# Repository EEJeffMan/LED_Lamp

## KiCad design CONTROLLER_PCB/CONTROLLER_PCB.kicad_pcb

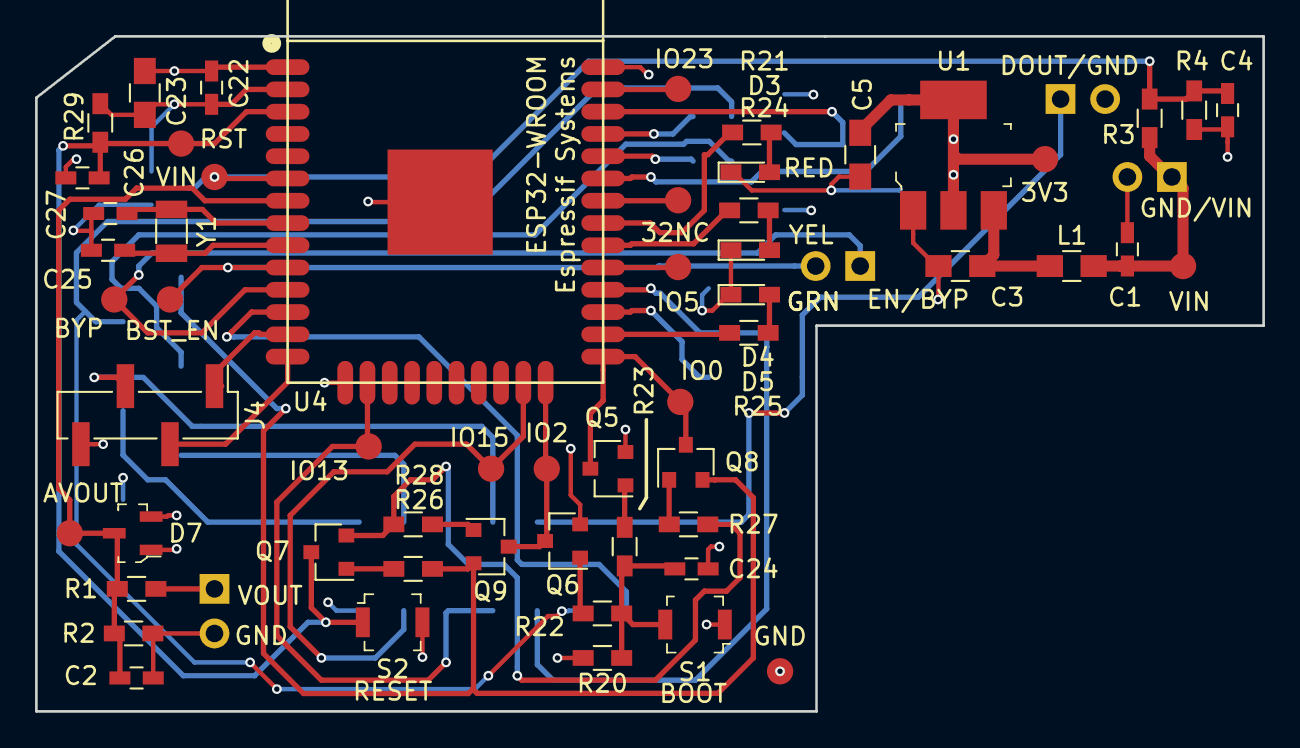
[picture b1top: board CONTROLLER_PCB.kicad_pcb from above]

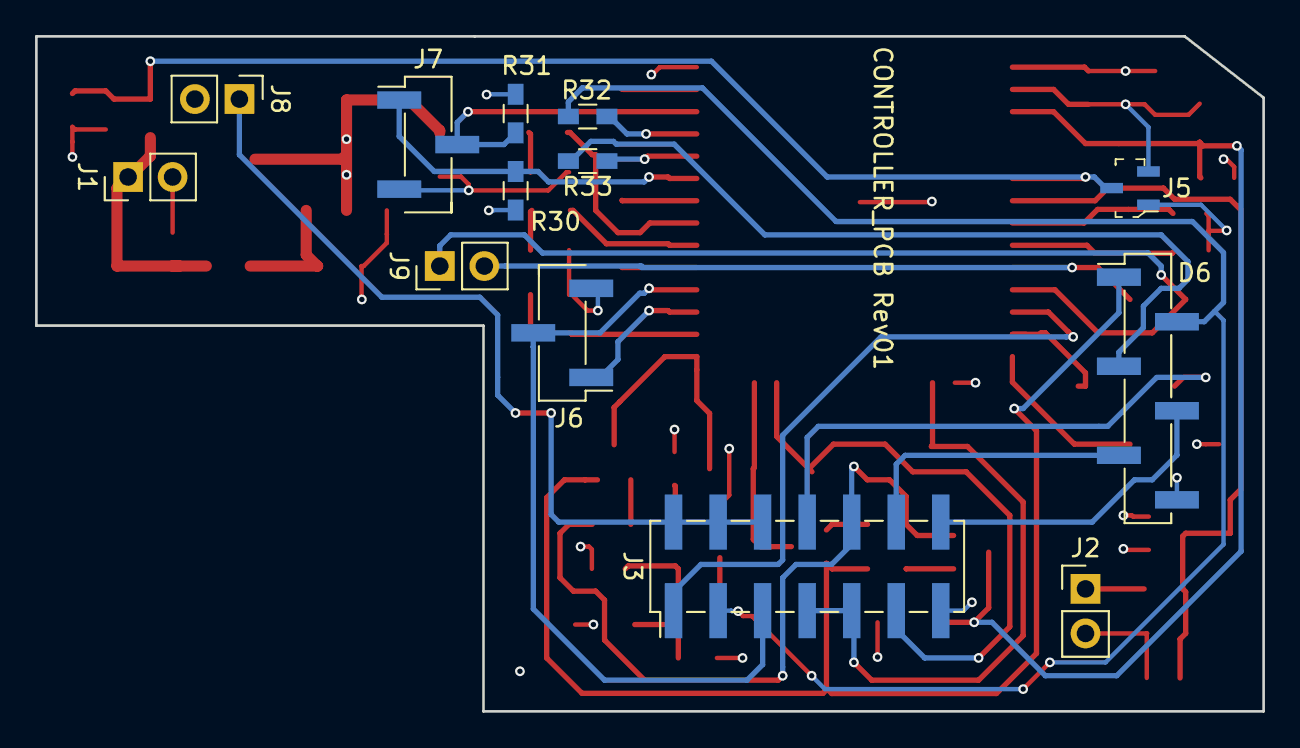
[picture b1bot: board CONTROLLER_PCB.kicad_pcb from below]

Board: 4 copper layers, 70.0 x 38.5 mm, 69 parts (13 on the bottom side), 48 nets.

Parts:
3V3, 32NC: TEST; Measurement_Point_Round-SMD-Pad_Small
AVOUT: TEST; Measurement_Point_Round-SMD-Pad_Small
BST_EN: TEST; Measurement_Point_Round-SMD-Pad_Small
BYP: TEST; Measurement_Point_Round-SMD-Pad_Small
C1, C2, C4, C22, C24, C27: 0.1uF; C_0603_HandSoldering
C3, C5, C23: 10uF; C_0805_HandSoldering
C25, C26: C_Small; C_0603_HandSoldering
D3: Red; LED_0603_HandSoldering
D4: Yellow; LED_0603_HandSoldering
D5: Green; LED_0603_HandSoldering
D6, D7: BAT54S-7-F; SOT-23-3
GND: TEST; Measurement_Point_Round-SMD-Pad_Small
IO0, IO2, IO5, IO13, IO15, IO23: TEST; Measurement_Point_Round-SMD-Pad_Small
J1, J2, J8, J9: Conn_01x02; Pin_Header_Straight_1x02_Pitch2.54mm
J3: Conn_02x07_Odd_Even; Pin_Header_Straight_2x07_Pitch2.54mm_SMD
J4: Conn_01x04; Pin_Header_Straight_1x04_Pitch2.54mm_SMD_Pin1Left
J5: Conn_01x06; Pin_Header_Straight_1x06_Pitch2.54mm_SMD_Pin1Left
J6, J7: Conn_01x03; Pin_Header_Straight_1x03_Pitch2.54mm_SMD_Pin1Left
L1: Ferrite_Bead; C_0805_HandSoldering
Q5, Q6: Q_NMOS_GSD; SOT-23
Q7, Q8, Q9: Q_NPN_BEC; SOT-23
R1, R3, R21, R22, R23, R24, R25, R26, R27, R28, R29: 10k; R_0603_HandSoldering
R2: 1k; R_0603_HandSoldering
R4: 2.49k; R_0603_HandSoldering
R20: 100k; R_0603_HandSoldering
R30, R31: 2.2k; R_0603_HandSoldering
R32, R33: 0 OHM; R_0603_HandSoldering
RST: TEST; Measurement_Point_Round-SMD-Pad_Small
S1, S2: B3U-1000P; Switch_Tactile_SMD_B3U-1000P
U1: AZ1117CH-3_3TRG1; SOT-223
U4: ESP32-WROOM
VIN: TEST; Measurement_Point_Round-SMD-Pad_Small
VIN#2: TEST; Measurement_Point_Round-SMD-Pad_Small
Y1: 32.768 kHz; Crystal_SMD_3215-2pin_3.2x1.5mm

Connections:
3V3_UART: J3.14, J5.4
32KHZ_IN: C26.1, U4.8, Y1.2
32KHZ_OUT: C25.1, U4.9, Y1.1
+3V3: 3V3.1, C5.1, C22.1, C23.1, D6.2, D7.2, J3.13, R29.1, R30.1, R31.1, S1.1, U1.2, U1.4, U4.2
ADC_VIN: C4.1, D6.3, R3.2, R4.1, RST.1, U4.6
ADC_VOUT: AVOUT.1, C2.1, D7.3, R1.2, R2.1, U4.7
BOOST_BYPASS: BYP.1, J9.1, U4.11
BOOST_EN: BST_EN.1, J9.2, U4.10
DOUT: J3.2, J3.4, J3.6, J8.1
DO_0: J3.1, U4.12
GND: C1.2, C2.2, C3.2, C4.2, C5.2, C22.2, C23.2, C24.2, C25.2, C26.2, C27.2, D3.1, D4.1, D5.1, D6.1, D7.1, GND.1, J1.2, J2.2, J4.4, J5.6, J6.3, J7.3, J8.2, Q5.2, Q6.2, R2.2, R4.2, R20.2, S2.2, U1.1, U4.1, U4.15, U4.38, U4.39
I2C_SCL: J7.2, R31.2, U4.36
I2C_SDA: J7.1, R30.2, U4.33
IO0: IO0.1, Q5.3, Q8.3, U4.25
IO2: IO2.1, Q6.3, Q9.3, U4.24
IO13: IO13.1, J3.7, J3.9, U4.16
IO15: IO15.1, J3.11, U4.23
LED_GREEN: R25.1, U4.26
LED_RED: R21.1, U4.31
LED_YELLOW: R24.1, U4.30
unnamed: C3.1, L1.1, U1.3
unnamed: C24.1, R20.1, R22.1, R23.1, S1.2
unnamed: D3.2, R21.2
unnamed: D4.2, R24.2
unnamed: D5.2, R25.2
unnamed: J2.1, R1.1
unnamed: Q5.1, R23.2
unnamed: Q6.1, R22.2
unnamed: Q7.1, R26.2
unnamed: Q8.1, R27.2
unnamed: Q9.1, R28.2
unnamed: R32.1, U4.35
unnamed: R33.1, U4.34
unnamed: IO23.1, U4.37
unnamed: 32NC.1, U4.32
unnamed: IO5.1, U4.29
RXDI: J5.3, R33.2
SPI_MISO: J4.2, U4.14
SPI_MOSI: J3.8, J4.3
SPI_SCK: J4.1, U4.13
TXDO: J3.3, J5.2, R32.2
U2RXD: J6.1, U4.27
U2TXD: J3.5, J6.2, U4.28
Vin: C1.1, J1.1, L1.2, R3.1, VIN.1
~CTS: J3.12, J5.5
~DTR: J5.1, Q8.2, Q9.2, R26.1
~RST: C27.1, Q7.3, R29.2, S2.1, U4.3, VIN#2.1
~RTS: J3.10, Q7.2, R27.1, R28.1

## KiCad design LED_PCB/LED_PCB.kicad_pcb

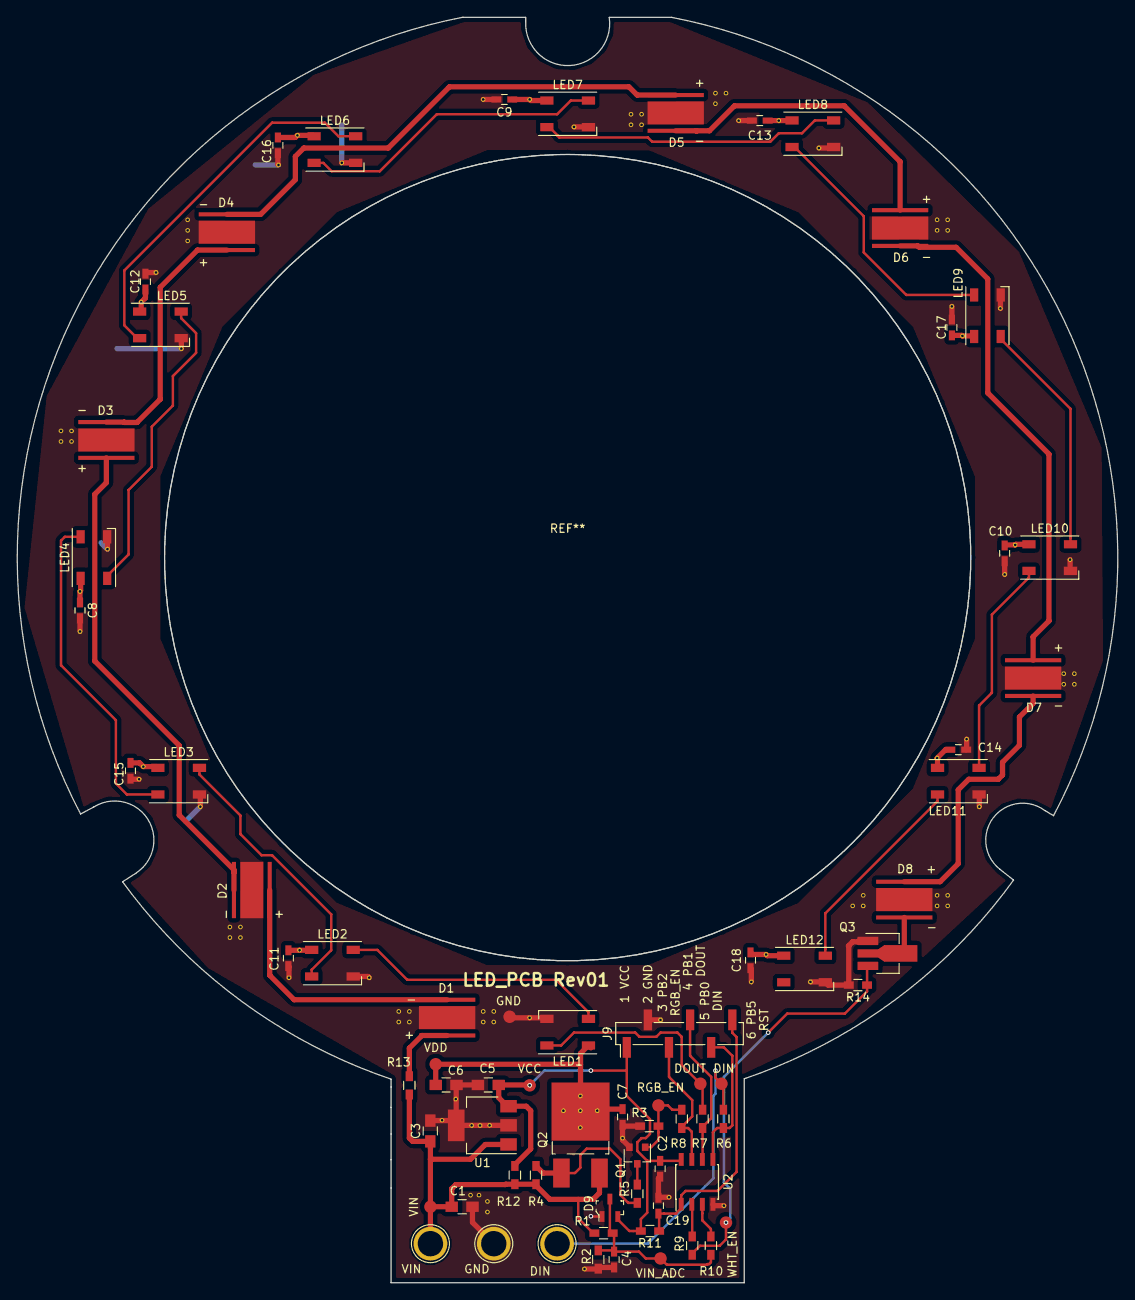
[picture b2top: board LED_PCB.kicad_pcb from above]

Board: 2 copper layers, 132.4 x 152.3 mm, 72 parts (0 on the bottom side), 37 nets.

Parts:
C1, C3, C5, C6: 4.7uF; C_0805_HandSoldering
C2, C4, C7, C8, C9, C10, C11, C12, C13, C14, C15, C16, C17, C18: 0.1uF; C_0603_HandSoldering
C19: 1000pF; C_0603_HandSoldering
D1, D2, D3, D4, D5, D6, D7, D8: XMLBWT-x; CREE-XM-L_HAND_SOLDERED
D9: BAT54S-7-F; SOT-23-3
DIN: TEST_1P; 1pin
DIN#2: TEST_1P; Measurement_Point_Round-SMD-Pad_Small
DOUT: TEST_1P; Measurement_Point_Round-SMD-Pad_Small
GND: TEST_1P; 1pin
GND#2: TEST_1P; Measurement_Point_Round-SMD-Pad_Small
J9: Conn_01x06; Pin_Header_Straight_1x06_Pitch2.54mm_SMD_Pin1Left
LED1, LED2, LED3, LED4, LED5, LED6, LED7, LED8, LED9, LED10, LED11, LED12: WS2812B; LED_WS2812B-PLCC4
Q1: Q_NMOS_GSD; SOT-23
Q2: Q_PMOS_GDS; TO-252-2_Rectifier
Q3: Q_NMOS_SDG; SOT-89-3_Handsoldering
R1, R2, R6, R7, R8, R9: 1k; R_0603_HandSoldering
R3, R4, R11, R14: 10k; R_0603_HandSoldering
R5, R10, R12, R13: 0 OHM; R_0603_HandSoldering
RGB_EN: TEST_1P; Measurement_Point_Round-SMD-Pad_Small
U1: MIC5233-3.3YS-TR; SOT-223
U2: ATTINY85-20SU; SOIC-8_3.9x4.9mm_Pitch1.27mm
VCC: TEST_1P; Measurement_Point_Round-SMD-Pad_Small
VDD: TEST_1P; Measurement_Point_Round-SMD-Pad_Small
VIN: TEST_1P; 1pin
VIN#2: TEST_1P; Measurement_Point_Round-SMD-Pad_Small
VIN_ADC: TEST_1P; Measurement_Point_Round-SMD-Pad_Small
WHT_EN: TEST_1P; Measurement_Point_Round-SMD-Pad_Small

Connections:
DIN: DIN.1, DIN#2.1, R6.2
DOUT: DOUT.1, LED1.4, R7.2
GND: C1.2, C2.2, C3.2, C4.2, C5.2, C6.2, C7.2, C8.2, C9.2, C10.2, C11.2, C12.2, C13.2, C14.2, C15.2, C16.2, C17.2, C18.2, C19.1, D1.3, D2.3, D3.3, D4.3, D5.3, D6.3, D7.3, D8.3, D9.1, GND.1, GND#2.1, J9.2, LED1.3, LED2.3, LED3.3, LED4.3, LED5.3, LED6.3, LED7.3, LED8.3, LED9.3, LED10.3, LED11.3, LED12.3, Q1.2, Q3.1, R2.2, R3.2, R14.2, U1.2, U1.4, U2.4
unnamed: C1.1, C3.1, Q2.3, R1.1, R4.1, R12.1, R13.2, U1.1, VIN.1, VIN#2.1
unnamed: C19.2, J9.6, R11.1, U2.1
unnamed: D1.1, D2.2
unnamed: D1.2, R13.1
unnamed: D2.1, D3.2
unnamed: D3.1, D4.2
unnamed: D4.1, D5.2
unnamed: D5.1, D6.2
unnamed: D6.1, D7.2
unnamed: D7.1, D8.2
unnamed: D8.1, Q3.2
unnamed: J9.3, R8.1, U2.7
unnamed: J9.4, R7.1, U2.6
unnamed: J9.5, R6.1, U2.5
unnamed: LED1.2, LED2.4
unnamed: LED2.2, LED3.4
unnamed: LED3.2, LED4.4
unnamed: LED4.2, LED5.4
unnamed: LED5.2, LED6.4
unnamed: LED6.2, LED7.4
unnamed: LED7.2, LED8.4
unnamed: LED8.2, LED9.4
unnamed: LED10.2, LED11.4
unnamed: LED9.2, LED10.4
unnamed: LED11.2, LED12.4
unnamed: Q1.3, R5.2
unnamed: Q2.1, R4.2, R5.1
unnamed: R9.1, U2.2
unnamed: R10.1, U2.3
RGB_EN: Q1.1, R3.1, R8.2, RGB_EN.1
VCC: C2.1, C5.1, D9.2, J9.1, R11.2, R12.2, U1.3, U2.8, VCC.1
VDD: C6.1, C7.1, C8.1, C9.1, C10.1, C11.1, C12.1, C13.1, C14.1, C15.1, C16.1, C17.1, C18.1, LED1.1, LED2.1, LED3.1, LED4.1, LED5.1, LED6.1, LED7.1, LED8.1, LED9.1, LED10.1, LED11.1, LED12.1, Q2.2, VDD.1
VIN_ADC: C4.1, D9.3, R1.2, R2.1, R10.2, VIN_ADC.1
WHITE_EN: Q3.3, R9.2, R14.1, WHT_EN.1

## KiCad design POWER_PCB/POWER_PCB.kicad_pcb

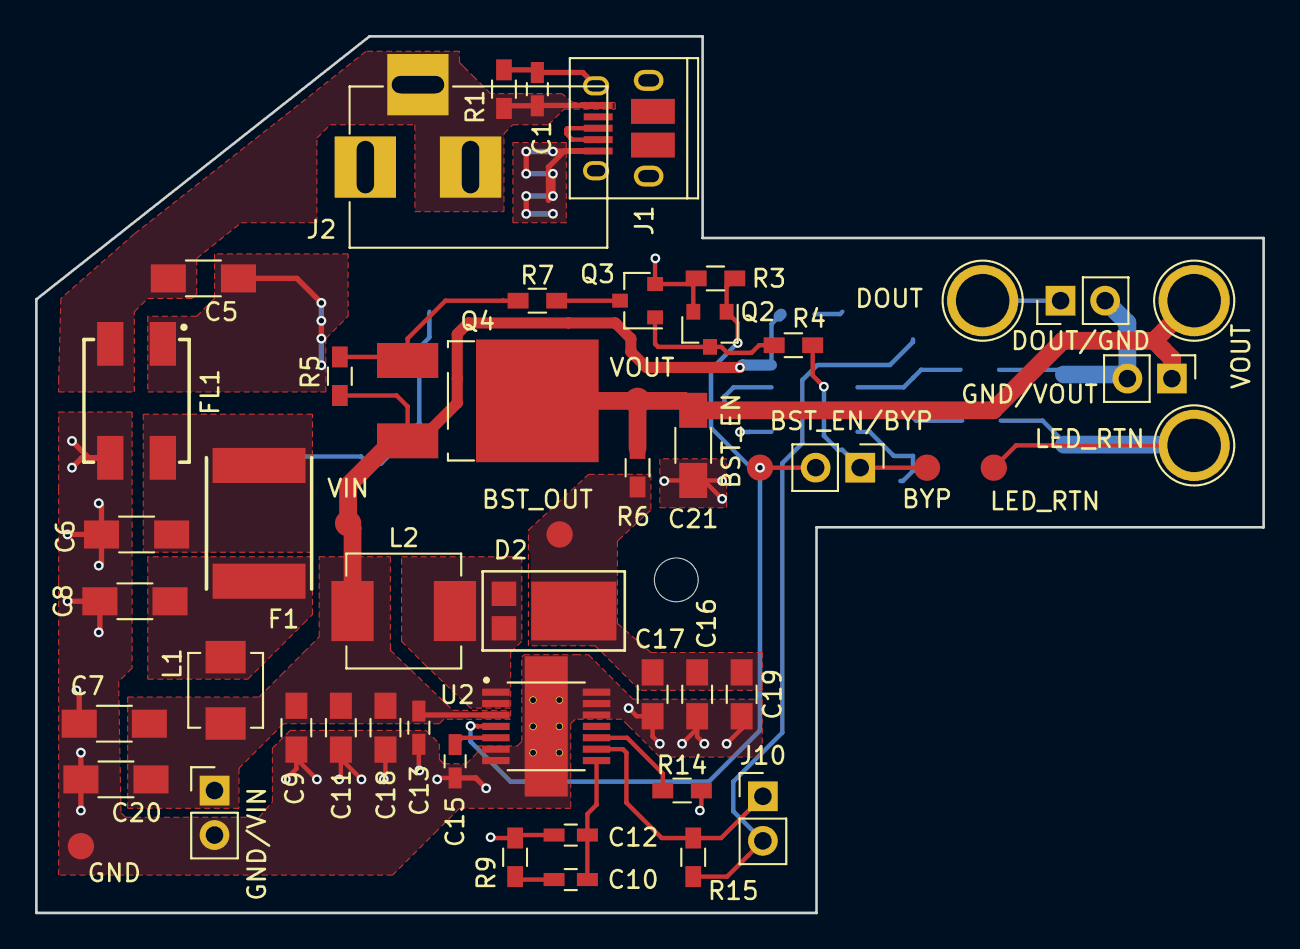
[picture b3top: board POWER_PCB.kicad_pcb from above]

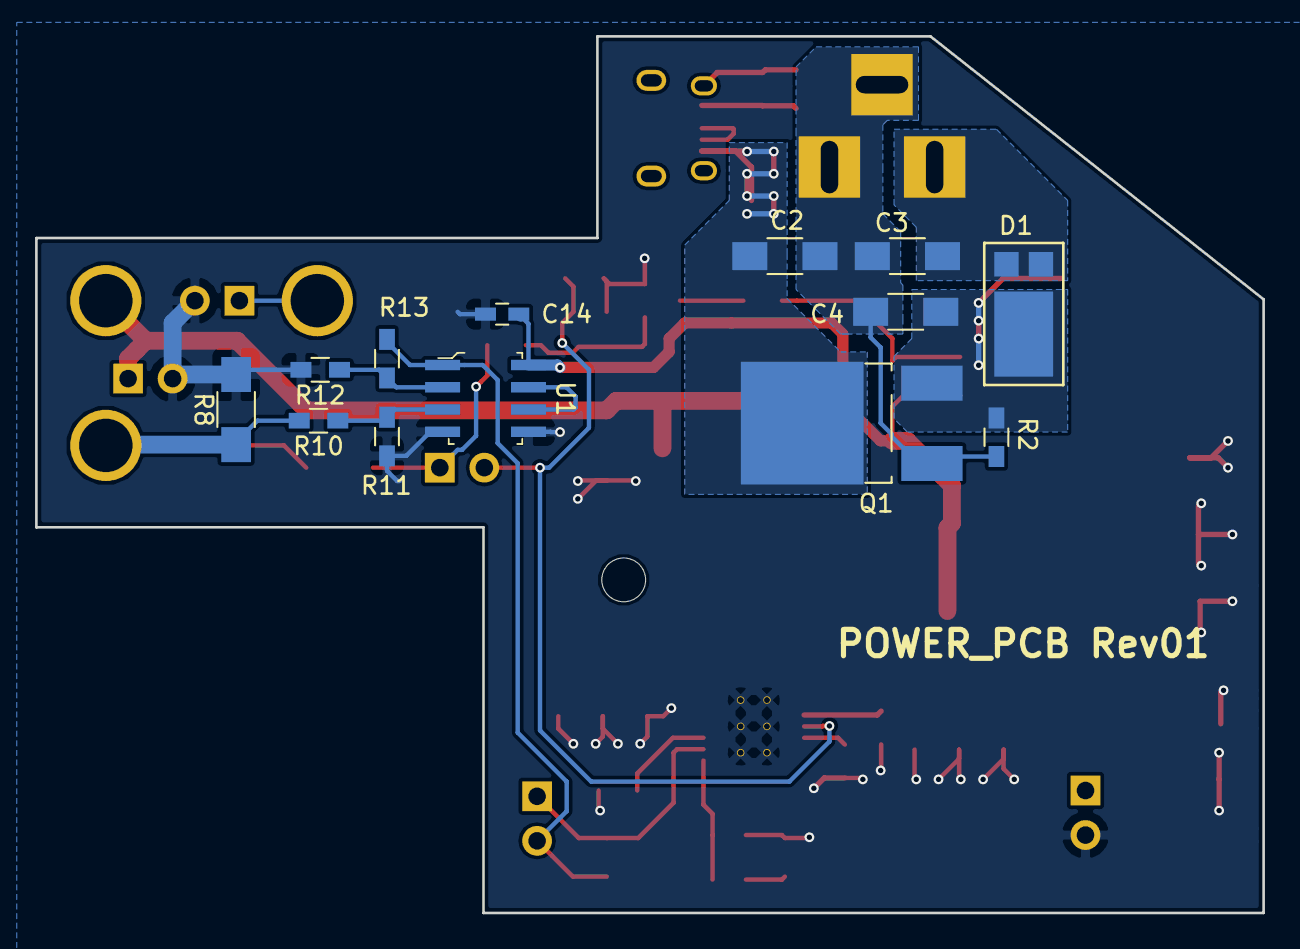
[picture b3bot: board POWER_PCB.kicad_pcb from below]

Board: 2 copper layers, 70.0 x 50.0 mm, 65 parts (13 on the bottom side), 29 nets.

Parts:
BST_EN: TEST; Measurement_Point_Round-SMD-Pad_Small
BST_EN/BYP: Conn_01x02; Pin_Header_Straight_1x02_Pitch2.54mm
BST_OUT: TEST; Measurement_Point_Round-SMD-Pad_Small
BYP: TEST; Measurement_Point_Round-SMD-Pad_Small
C1, C12: 100p; C_0603_HandSoldering
C2, C3, C4, C5, C6, C7, C8, C20, C21: 22uF; C_1206_HandSoldering
C9, C11, C16, C17, C18, C19: 10uF; C_0805_HandSoldering
C10, C13, C14: 0.1uF; C_0603_HandSoldering
C15: 0.01uF; C_0603_HandSoldering
D1, D2: D_Schottky_AKA; Diodes_Incorporated_POWERDI_5
DOUT: Conn_01x01; 1pin
DOUT/GND: Conn_01x02; Pin_Header_Straight_1x02_Pitch2.54mm
F1: Polyfuse; 2920L
FL1: EMI_Filter_LL_14_23; FIL_ACM70V-701-2PL-TL00
GND: TEST; Measurement_Point_Round-SMD-Pad_Small
GND/VIN: Conn_01x02; Pin_Header_Straight_1x02_Pitch2.54mm
GND/VOUT: Conn_01x02; Pin_Header_Straight_1x02_Pitch2.54mm
J1: 10103594-0001LF; USB_Micro-B_10103594-0001LF
J2: Barrel_Jack; BARREL_JACK
J10: Conn_01x02; Pin_Header_Straight_1x02_Pitch2.54mm
L1: 1uH; L_Vishay_IHLP-1616
L2: 10uH; L_Vishay_IHLP-2525
LED_RTN: Conn_01x01; 1pin
LED_RTN#2: TEST; Measurement_Point_Round-SMD-Pad_Small
Q1, Q4: Q_PMOS_GDS; TO-252-2_Rectifier
Q2, Q3: Q_NMOS_GSD; SOT-23
R1: 1M; R_0603_HandSoldering
R2: 20k; R_0603_HandSoldering
R3, R5, R11, R13: 10k; R_0603_HandSoldering
R4, R10, R12: 1k; R_0603_HandSoldering
R6, R7: 0 OHM; R_0603_HandSoldering
R8: 0.25 OHM; R_1206_HandSoldering
R9: 2.2k; R_0603_HandSoldering
R14: 30k; R_0603_HandSoldering
R15: 100 OHM; R_0603_HandSoldering
U1: TS462CDT; SOIC-8_W3.9mm
U2: TPS55340PWP; SOP65P640X120-15N_HAND_SOLDERING
VIN: TEST; Measurement_Point_Round-SMD-Pad_Small
VOUT: Conn_01x01; 1pin
VOUT#2: TEST; Measurement_Point_Round-SMD-Pad_Small

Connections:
/Input_Output/Vout: C21.1, GND/VOUT.1, Q4.2, R6.1, VOUT.1, VOUT#2.1
BOOST_BYPASS: BST_EN/BYP.1, BYP.1, R4.2
BOOST_EN: BST_EN.1, BST_EN/BYP.2, Q2.1, R3.1, U2.4
BOOST_OUT: BST_OUT.1, C16.1, C17.1, C19.1, D2.2, R6.2
DOUT: DOUT.1, DOUT/GND.1
GND: C6.2, C7.2, C8.2, C9.2, C11.2, C12.2, C13.2, C14.2, C15.2, C16.2, C17.2, C18.2, C19.2, C20.2, C21.2, DOUT/GND.2, FL1.3, GND.1, GND/VIN.2, GND/VOUT.2, Q2.2, Q3.2, R3.2, R8.2, R9.2, R11.2, R12.2, R14.2, U1.4, U1.5, U2.6, U2.7, U2.12, U2.13, U2.14, U2.15, U2.P$1, U2.P$2, U2.P$3, U2.P$4, U2.P$5, U2.P$6
LED_RTN: LED_RTN.1, LED_RTN#2.1, R8.1, R10.2
unnamed: C1.1, J1.6, R1.1
unnamed: C1.2, C2.2, C3.2, C4.2, C5.2, FL1.2, J1.5, J2.2, J2.3, Q1.1, R1.2, R2.2
unnamed: C2.1, J1.1, Q1.2
unnamed: C3.1, D1.1, D1.3, J2.1
unnamed: C4.1, C5.1, D1.2, FL1.1, Q1.3, R2.1
unnamed: C6.1, F1.2, FL1.4
unnamed: C8.1, F1.1, L1.1
unnamed: C10.1, C12.1, U2.8
unnamed: C10.2, R9.1
unnamed: C15.1, U2.5
unnamed: D2.1, D2.3, L2.2, U2.1, U2.2
unnamed: J1.2, J1.3
unnamed: J10.1, R15.1, U2.9
unnamed: J10.2, R13.1, R15.2, U1.1
unnamed: Q2.3, Q3.1, R4.1
unnamed: Q3.3, R7.2
unnamed: Q4.1, R5.2, R7.1
unnamed: R10.1, R11.1, U1.3
unnamed: R12.1, R13.2, U1.2
unnamed: R14.1, U2.10
unnamed: U1.6, U1.7
Vin: C7.1, C9.1, C11.1, C13.1, C14.1, C18.1, C20.1, GND/VIN.1, L1.2, L2.1, Q4.3, R5.1, U1.8, U2.3, VIN.1

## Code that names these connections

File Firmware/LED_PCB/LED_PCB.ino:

/*
 * Name: LED_LAMP
 * Author: EEJeffMan
 * Date: 3/9/19
 * 
 * Replace bulb in desk lamp with LEDs.
 * 
 * MCU is ATTINY85, using the guide below to install support for this chip in Arduino:
 *  http://highlowtech.org/?p=1695
 *  
 * This was found courtesy of the following post:
 *  https://oscarliang.com/program-attiny-micro-controller-using-arduino/
 *    
 * Hardware options for white or RGB LEDs
 *   White LEDs: 8 high power Cree LEDs, needs an external constant current regulator. Load is ~24V, target current is ~400mA max.
 *   RGB LEDs: 12 RGB LEDs, WS2812 or similar. Data lines connected in parallel. High side switch controlled by MCU to disable connection. Max input is ~5V.
 *      
 * Inputs:
 *   DIN (0): Data input to control operation.
 *   VIN_ADC (4,A2): input voltage
 *    
 * Outputs:
 *   DOUT (1): serial data for RGB LED's
 *   RGB_EN (2): Control of high side switch for power to RGB LEDs
 *   WHITE_EN (3): Control of low side switch for power to white LEDs
 * 
 * Description:
 *        
 *    Initially: both RGB_EN and WHITE_EN output low (outputs off).
 *    
 *    Read ADC input: 
 *      If input less than 5.5V: RGB LED mode.
 *      If input greater than 18V and less than 30V: White LED mode.
 *      Keep WHITE_EN on at all times unless voltage is > 30V. This is ok because
 *      the white LEDs will not draw any current unless input is greater than ~18V.
 *      RGB's must turn off when greater than ~5.5V to prevent damage.
 *    
 *    Use softwareserial to read input commands via DIN.
 *      
 *    RGB's use "FastLED" library, credit to tutorial in link below:
 *    https://howtomechatronics.com/tutorials/arduino/how-to-control-ws2812b-individually-addressable-leds-using-arduino/
 *    FastLED github: https://github.com/FastLED/FastLED
 *    
 *    Commands:
 *    
 *      LED_MODE_OFF      both off
 *      LED_MODE_WHITE    RGB off, white on
 *      LED_MODE_RGB      RGB on, set PWM via FastLED
 *      LED_MODE_RGB_SET  Set RGB colors with a set of bytes.
 *      
 */

#include <FastLED.h>
#include <SoftwareSerial.h>

#define NUM_LEDS      12
#define LED_PIN       1
#define COLOR_ORDER   GRB

// color table

/*
 * (R, G, B)
 * White (255, 255, 255)
 * Red (255, 0, 0)
 * Green (0, 255, 0)
 * Blue (0, 0, 255)
 * Yellow (255, 255, 0)
 * Cyan (0, 255, 255)
 * Magenta (255, 0, 255)
 * Silver (192, 192, 192)
 * Gray (128, 128, 128)
 * Maroon (128, 0, 0)
 */

 #define WHITE_R  255
 #define WHITE_G  255
 #define WHITE_B  255

 #define RED_R  255
 #define RED_G  0
 #define RED_B  0

 #define GREEN_R  0
 #define GREEN_G  255
 #define GREEN_B  0

 #define BLUE_R 0
 #define BLUE_G 0 
 #define BLUE_B 255

 #define YELLOW_R 255
 #define YELLOW_G 255
 #define YELLOW_B 0

 #define CYAN_R 0
 #define CYAN_G 255
 #define CYAN_B 255

 #define MAGENTA_R  255
 #define MAGENTA_G  0
 #define MAGENTA_B  255

 #define SILVER_R 192
 #define SILVER_G 192
 #define SILVER_B 192

 #define GRAY_R 128
 #define GRAY_G 128
 #define GRAY_B 128

 #define MAROON_R 128
 #define MAROON_G 0
 #define MAROON_B 0  

 #define PURPLE_R 127
 #define PURPLE_G 0
 #define PURPLE_B 255

// led mode defines
#define LED_MODE_OFF          0x10
#define LED_MODE_WHITE        0x20
#define LED_MODE_RGB          0x30
#define LED_MODE_RGB_SET      0x40

// pin definitions
#define WHITE_EN_PIN    3
#define RGB_EN_PIN      2
#define DIN_PIN         0
#define DOUT_PIN        1
#define VIN_ADC_PIN     A2  //A2, aruidno pin & port pin 4

// marcros for led output control functions
#define white_leds_on()     digitalWrite(WHITE_EN_PIN, HIGH);
#define white_leds_off()    digitalWrite(WHITE_EN_PIN, LOW);
#define rgb_leds_on()       digitalWrite(RGB_EN_PIN, HIGH);
#define rgb_leds_off()      digitalWrite(RGB_EN_PIN, LOW);

// indexes for RGB data array
#define RGB_DATA_RED    0
#define RGB_DATA_GREEN  1
#define RGB_DATA_BLUE   2

// max values for white and RGB LEDs
#define ADC_WHITE_MAX   1000
#define ADC_RGB_MAX     500

// function prototypes
unsigned int read_vin();
void set_led_mode (unsigned int mode);
unsigned int read_command(unsigned int command);

// global variables
unsigned int led_mode = LED_MODE_OFF;
unsigned int rgb_data[3];
unsigned int rgb_data_index = 0;

SoftwareSerial tinySerial(DOUT_PIN, DIN_PIN);   // DOUT is not actually UART, it is  taken over with the FastLED library below.
CRGB leds[NUM_LEDS];

void setup() {

  pinMode(DIN_PIN, INPUT);
  pinMode(DOUT_PIN, OUTPUT);
  pinMode(WHITE_EN_PIN, OUTPUT);
  pinMode(RGB_EN_PIN, OUTPUT);
  pinMode(VIN_ADC_PIN, INPUT);

  //initially, both outputs off
  led_mode = LED_MODE_OFF;
  set_led_mode(LED_MODE_OFF); //led_mode);

  tinySerial.begin(9600);
  
  // put your setup code here, to run once:
  FastLED.addLeds<WS2812, LED_PIN, COLOR_ORDER>(leds, NUM_LEDS);

  for (int i=0; i<NUM_LEDS; i++)
  {
    leds[i] = CRGB(PURPLE_R, PURPLE_G, PURPLE_B);//WHITE_R, WHITE_G, WHITE_B);
  }
  //FastLED.show();
}

void loop() {
  // put your main code here, to run repeatedly:

    // first, read vin and determine output mode (off, white LEDs, or RGB LEDs):    
    //led_mode = read_vin();
    // debugging: force RGB LED mode.
    led_mode = LED_MODE_RGB;
    
    // second, look for control command from data input
    /*if(tinySerial.available())
    { 
        led_mode = read_command( tinySerial.read() );
    }*/

    // debugging: force RGB colors to remain in the state set in setup()
    
    set_led_mode(led_mode);
    delay(10);    // 10 ms
}

unsigned int read_vin()
{
    unsigned int vin;
    unsigned int mode;
  
    vin = analogRead(VIN_ADC_PIN);

    if (vin > ADC_WHITE_MAX)
    {
        mode = LED_MODE_OFF;
    }
    else if (vin > ADC_RGB_MAX)    // less than white ma but greater than RGB max
    {
        mode = LED_MODE_WHITE;
    }
    else                           // low enough to safely run RGB LEDs.
    {
        mode = LED_MODE_RGB;
    }

    return mode;
}

void set_led_mode(unsigned int mode)
{
    switch(mode)
    {
        case LED_MODE_OFF:
          white_leds_off();
          rgb_leds_off();
        break;

        case LED_MODE_WHITE:
          white_leds_on();
          rgb_leds_off();
        break;

        case LED_MODE_RGB:
           white_leds_on();   //voltage will be too low for LEDs to draw current, so ok to leave this on.
           rgb_leds_on();
           FastLED.show();
        break;

        default:
            white_leds_off();
            rgb_leds_off();
            // set error code or send diagnostic message?
        break;
    }
}

unsigned int read_command(unsigned int data)
{
    /*
     *  input: serial command / data byte.
     *  
     *  LED_MODE_OFF      both off
     *  LED_MODE_WHITE    RGB off, white on
     *  LED_MODE_RGB      RGB on, set PWM via FastLED
     *  LED_MODE_RGB_SET  Set RGB colors with a set of bytes 
     *  
     *  the first 3 commands will directly determine how the output control pins should be set.
     *  
     *  the last command will trigger a sequence of serial bytes that contain RGB color data. Each byte will be sent every 50ms.
     *  
     *  first byte: blue data
     *  second byte: green data
     *  third byte: red data
     */
        static unsigned int mode;

        // NOTE: when this "if" is taken, mode is not changed, but it is still returned. the previous mode is retained.
        if (rgb_data_index)   // if index > 0, we are in the middle of transferring data.
        {
            rgb_data_index--;
          
            rgb_data[rgb_data_index] = data;

            // after the last byte is sent, update the DOUT output data being sent.
            if (0 == rgb_data_index)
            {
                for (int i=0; i<NUM_LEDS; i++)
                {
                  leds[i] = CRGB(GREEN_R, GREEN_G, GREEN_B);//(rgb_data{RGB_DATA_RED], rgb_data{RGB_DATA_GREEN], rgb_data{RGB_DATA_BLUE]);
                }
                FastLED.show();
            }
        }
        else
        {
            switch(data)
            {
                case LED_MODE_RGB_SET:
                    rgb_data_index = 3;     // this will start the data read sequence, which occurs in the "if" statement above.
                break;
                case LED_MODE_OFF:
                    mode = LED_MODE_OFF;
                break;
                case LED_MODE_WHITE:
                    mode = LED_MODE_WHITE;
                break;
                case LED_MODE_RGB:
                    mode = LED_MODE_RGB;
                break;
                default: 
                    mode = LED_MODE_OFF;
                break;
            }
        }

        return mode;
}

// end of file.

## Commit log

2019-01-26 Added LED_LAMP.xml
2019-01-26 First revision firmware
2019-01-31 Creating LED_PCB project
2019-01-31 Added symbols & wired schematic, need to assign values / PNs / footprints
2019-02-01 Finished schematic & BOM, started layout, need to define PCB shape
2019-02-03 Added housing outline and started board outline.
2019-02-03 Finished board outline, and started placing LEDs
2019-02-04 LED board: routed most of top layer... started controller PCB schematic.
2019-02-06 LED PCB: Changed to 2 layer, added vias and copper (not complete). Controller: Split up ESP32 and input & power sheets in schematic.
2019-02-08 Added components to LED PCB sch and updated layout
    Still need to add thermals for white LEDs and then run error check...
2019-02-08 Finished layout and created gerbers.
2019-02-09 Updated layout to add giant mounting hole for center opening; ordered PCB's with this design.
2019-02-09 Created ESP32 pinout spreadsheet, finished MCU pinout, and added MCU_SUPPORT schematic sheet.
2019-02-10 Added input filtering, and assigned footprints to most components, several remain.
2019-02-11 Finalized schematic, created BOM, started placement (no PCB size yet)
2019-02-11 Updated placement...
2019-02-23 Updated BOM & added PCB shape to layout... this is right before removing power supply components...
2019-02-23 Split up power supply and MCU into 2 different boards, schematic design not complete.
2019-02-26 Updated POWER_PCB & CONTROLLER_PCB sch's and layouts
2019-02-27 Finished controller layout, and 80% done with power PCB layout.
2019-03-01 Finished copper, silkscreen and gerbers for power PCB and controller PCBs,
2019-03-09 Created source code for LED board MCU.
2019-03-09 Many updates for LED_PCB MCU firmware.
2019-03-10 Updates to LED_PCB MCU firmware.
2019-03-11 Added FastLED library to repo, modified some code for improved bring-up verification, and added comments regarding setting up ATTINY in arduino IDE.
2019-11-08 Added waveforms of boost with 100k freq resistor, white LEDs at 0.3 ohm sense and 10k/1k gain
